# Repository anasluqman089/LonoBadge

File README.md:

# LonoBadge

This project is a small custom electronic badge built around the **Seeed Studio XIAO nRF52840** and a **Waveshare 1.54-inch 200×200 e-Paper display**.

The main idea is simple: connect the badge to a computer using USB-C, send a picture to it, and have the picture appear on the e-Paper display. Because the display is e-Paper, the image stays visible even after the display stops refreshing.

## BOM

* 1x Seeed Studio XIAO nRF52840
* 1x 1.54-inch 200×200 monochrome e-Paper Module
* 1 × push button
* 1x CR2032 Coin Cell Battery
* 1x CR2032 Coin Cell Battery holder

## Pin Connections

The badge uses the following pin arrangement:

```text
XIAO nRF52840       Waveshare e-Paper
--------------------------------------
D1                  CS
D2                  DC
D3                  RST
D4                  BUSY
D8                  CLK
D10                 MOSI
3V3_OUT             3.3V
GND                 GND
```

The button is connected like this:

```text
D5 ───── Push Button ───── GND
```

The firmware uses the internal pull-up resistor, so the button is normally HIGH and becomes LOW when pressed.

## How It Works

The badge communicates with the computer through the XIAO nRF52840's USB connection.

When a picture is selected on the computer, it is converted into a **200×200 black-and-white image**. The image is then sent to the XIAO through USB.

The XIAO receives the image and stores it temporarily in memory. It then sends the image to the Waveshare e-Paper display through SPI.

The basic process is:

```text
Picture on PC
     ↓
Convert to 200×200
     ↓
Convert to black & white
     ↓
USB-C
     ↓
XIAO nRF52840
     ↓
SPI
     ↓
Waveshare e-Paper
     ↓
Picture displayed
```

## Image Format

The current firmware is designed for:

Resolution: 200 × 200 pixels
Colour:     Black & White
Format:     1-bit bitmap data
Data size:  5000 bytes

## Button

The single button is connected to **D5**.

When the button is pressed, the XIAO refreshes the current image on the e-Paper display.

This can be useful if the display needs to be refreshed or if you want the button to become part of the badge's user interface later.

## Arduino Library

The firmware uses the **GxEPD2** library to control the e-Paper display.

Install the library through the Arduino IDE:

```text
Arduino IDE
    ↓
Library Manager
    ↓
Search: GxEPD2
    ↓
Install
```

The sketch also uses the standard Arduino SPI functionality.

## Uploading the Firmware

Open the `.ino` file in Arduino IDE.

Select:

```text
Board:
Seeed XIAO nRF52840
```

Then select the COM port belonging to the XIAO.

Connect the XIAO to the computer using USB-C and upload the firmware.

After the upload finishes, the e-Paper should show the startup screen and the serial monitor should report that the badge is ready.

## Sending a Picture

The firmware expects the computer to send the following header:

```text
IMG200
```

followed by exactly **5000 bytes** of image data.

A separate PC-side uploader can take a normal PNG or JPG image, resize it to 200×200, convert it to black and white, and send it to the XIAO.

For example:

```text
python upload_badge.py COM5 badge.png
```

Replace `COM5` with the COM port assigned to your XIAO.

## Current Limitations

The current version is intentionally simple.

It supports one 200×200 monochrome image at a time. The image is transferred through USB rather than making the XIAO behave like a USB flash drive.

The current button also only refreshes the image. It can be expanded later to support different images, menus, animations, or other badge functions.

The exact GxEPD2 display driver also depends on the controller used by the specific Waveshare 1.54-inch module. If the display does not initialize correctly, the exact Waveshare model should be checked before changing the wiring or firmware.

# Picture

## Schematic

## PCB

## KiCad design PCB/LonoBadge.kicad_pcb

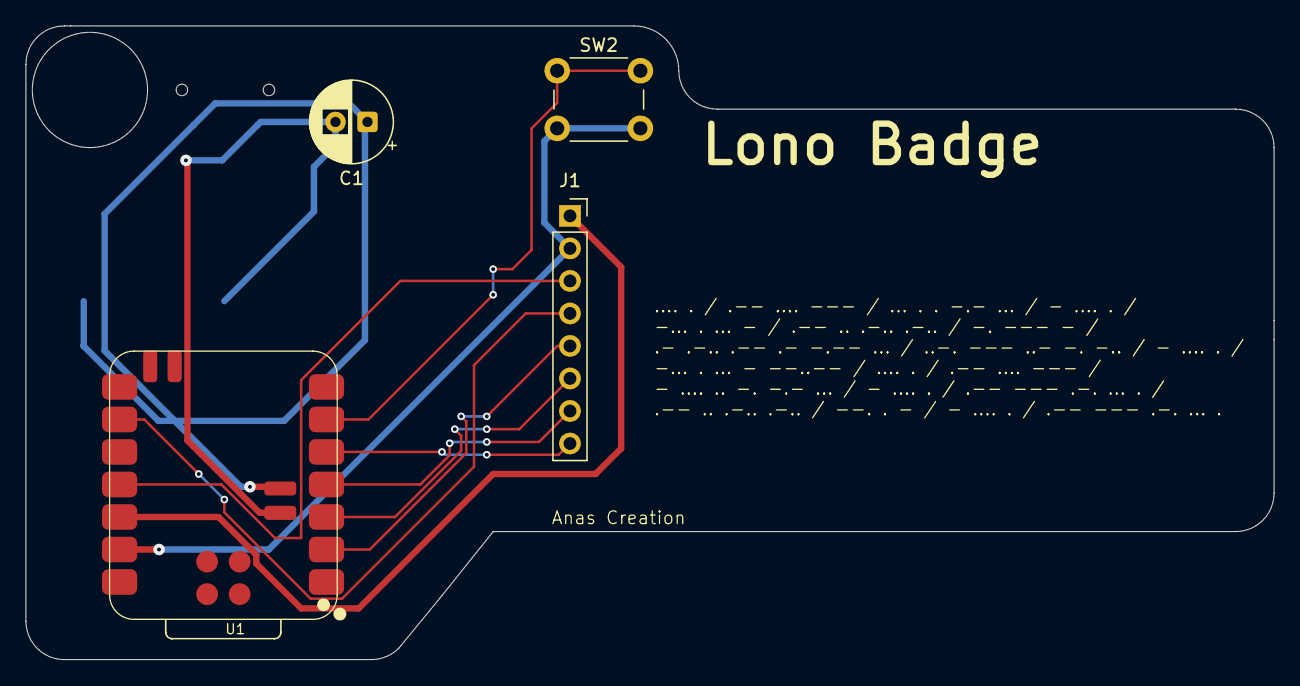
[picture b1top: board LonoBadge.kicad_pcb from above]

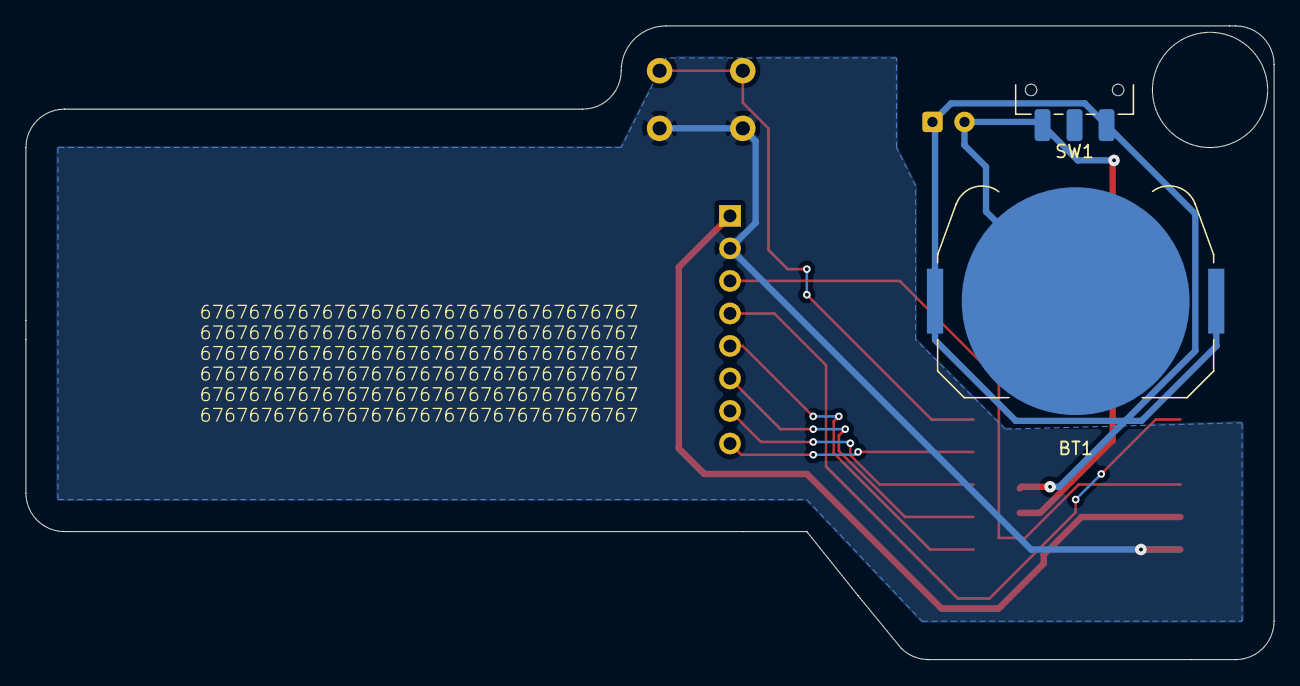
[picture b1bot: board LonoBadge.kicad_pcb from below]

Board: 2 copper layers, 97.5 x 49.5 mm, 6 parts (2 on the bottom side), 11 nets.

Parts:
BT1: Battery_Cell; BatteryHolder_Keystone_3034_1x20mm
C1: C; CP_Radial_D6.3mm_P2.50mm
J1: Conn_01x08_Socket; PinSocket_1x08_P2.54mm_Vertical
SW1: SW_SPDT; SW_SPDT_CK_JS102011SAQN
SW2: SW_Push; SW_PUSH_6mm
U1: XIAO-nRF52840-SMD

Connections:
+3.3V: J1.1, U1.12 (3V3_OUT)
/BSY: J1.8, U1.5 (D4)
/CLK: J1.4, U1.9 (D8)
/CS: J1.5, U1.2 (D1)
/DC: J1.6, U1.3 (D2)
/MOSI: J1.3, U1.11 (D10)
/RST: J1.7, U1.4 (D3)
/SW1: SW2.1, U1.6 (D5)
GND: J1.2, SW2.2, U1.13 (GND)
unnamed: BT1.1 (+), C1.1, SW1.1 (A), U1.19 (VBAT)
unnamed: BT1.2 (-), C1.2, SW1.3 (C), U1.20 (GND)
